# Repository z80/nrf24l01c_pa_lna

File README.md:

# Radio board with Power Amplifier.

A 2.4GHz generic radio communication board based on NRF24L01+ Nordic radio chip and RFX2101C Power Amplifier chip.

It is equipped with an on-board 3.3V linear regulator. So, it hasn't ever been noticed loosing a connection or malfunctioning due to power rail voltage fluctuations if powered with anything above 3.7V.

Thermal design turned out to be good. At max power and constant carrier mode the board consumes ~200mA of current. But neither part gets hot. The whole board heats up evenly and is just warm on touch.

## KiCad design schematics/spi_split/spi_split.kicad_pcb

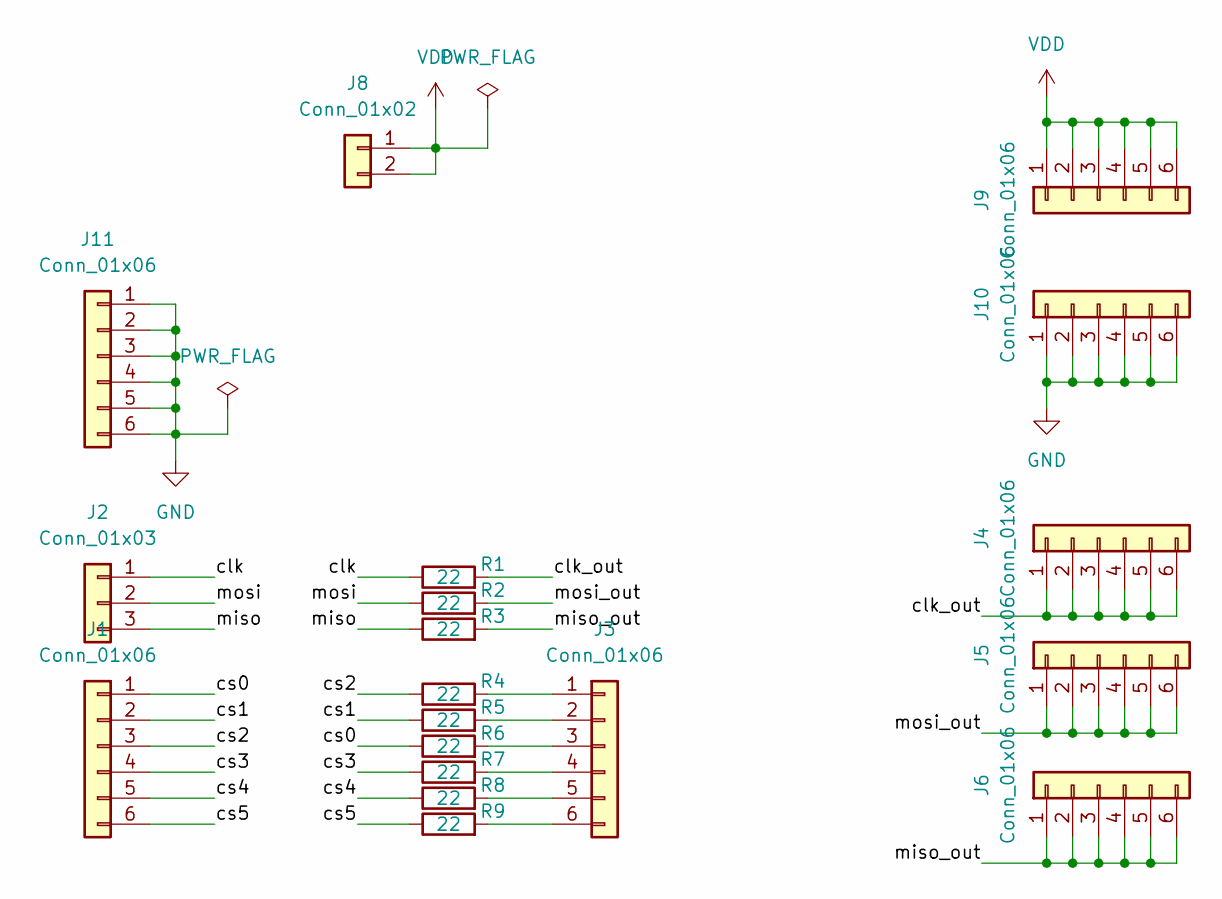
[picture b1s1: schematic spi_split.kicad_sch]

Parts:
J1, J3, J4, J5, J6, J9, J10, J11: Conn_01x06; PinHeader_1x06_P2.54mm_Vertical
J2: Conn_01x03; PinHeader_1x03_P2.54mm_Vertical
J8: Conn_01x02; PinHeader_1x02_P2.54mm_Vertical
R1, R2, R3, R4, R5, R6, R7, R8, R9: 22; R_0603_1608Metric

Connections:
/clk: J2.1, R1.1
/clk_out: J4.1, J4.2, J4.3, J4.4, J4.5, J4.6, R1.2
/cs0: J1.1, R6.1
/cs1: J1.2, R5.1
/cs2: J1.3, R4.1
/cs3: J1.4, R7.1
/cs4: J1.5, R8.1
/cs5: J1.6, R9.1
/miso: J2.3, R3.1
/miso_out: J6.1, J6.2, J6.3, J6.4, J6.5, J6.6, R3.2
/mosi: J2.2, R2.1
/mosi_out: J5.1, J5.2, J5.3, J5.4, J5.5, J5.6, R2.2
GND: J10.1, J10.2, J10.3, J10.4, J10.5, J10.6, J11.1, J11.2, J11.3, J11.4, J11.5, J11.6
unnamed: J3.1, R4.2
unnamed: J3.2, R5.2
unnamed: J3.3, R6.2
unnamed: J3.4, R7.2
unnamed: J3.5, R8.2
unnamed: J3.6, R9.2
VDD: J8.1, J8.2, J9.1, J9.2, J9.3, J9.4, J9.5, J9.6

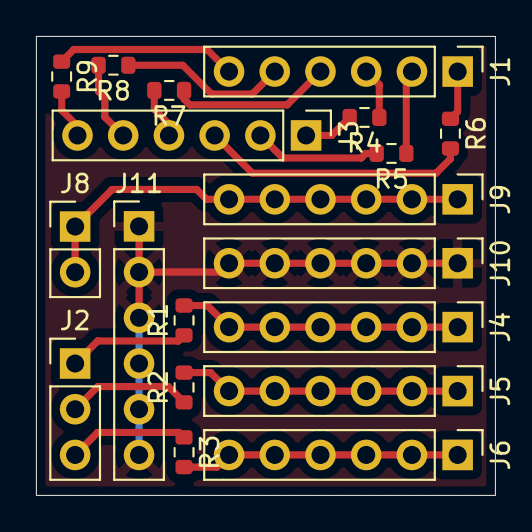
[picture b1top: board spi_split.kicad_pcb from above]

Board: 2 copper layers, 25.5 x 25.5 mm, 19 parts (0 on the bottom side), 20 nets.

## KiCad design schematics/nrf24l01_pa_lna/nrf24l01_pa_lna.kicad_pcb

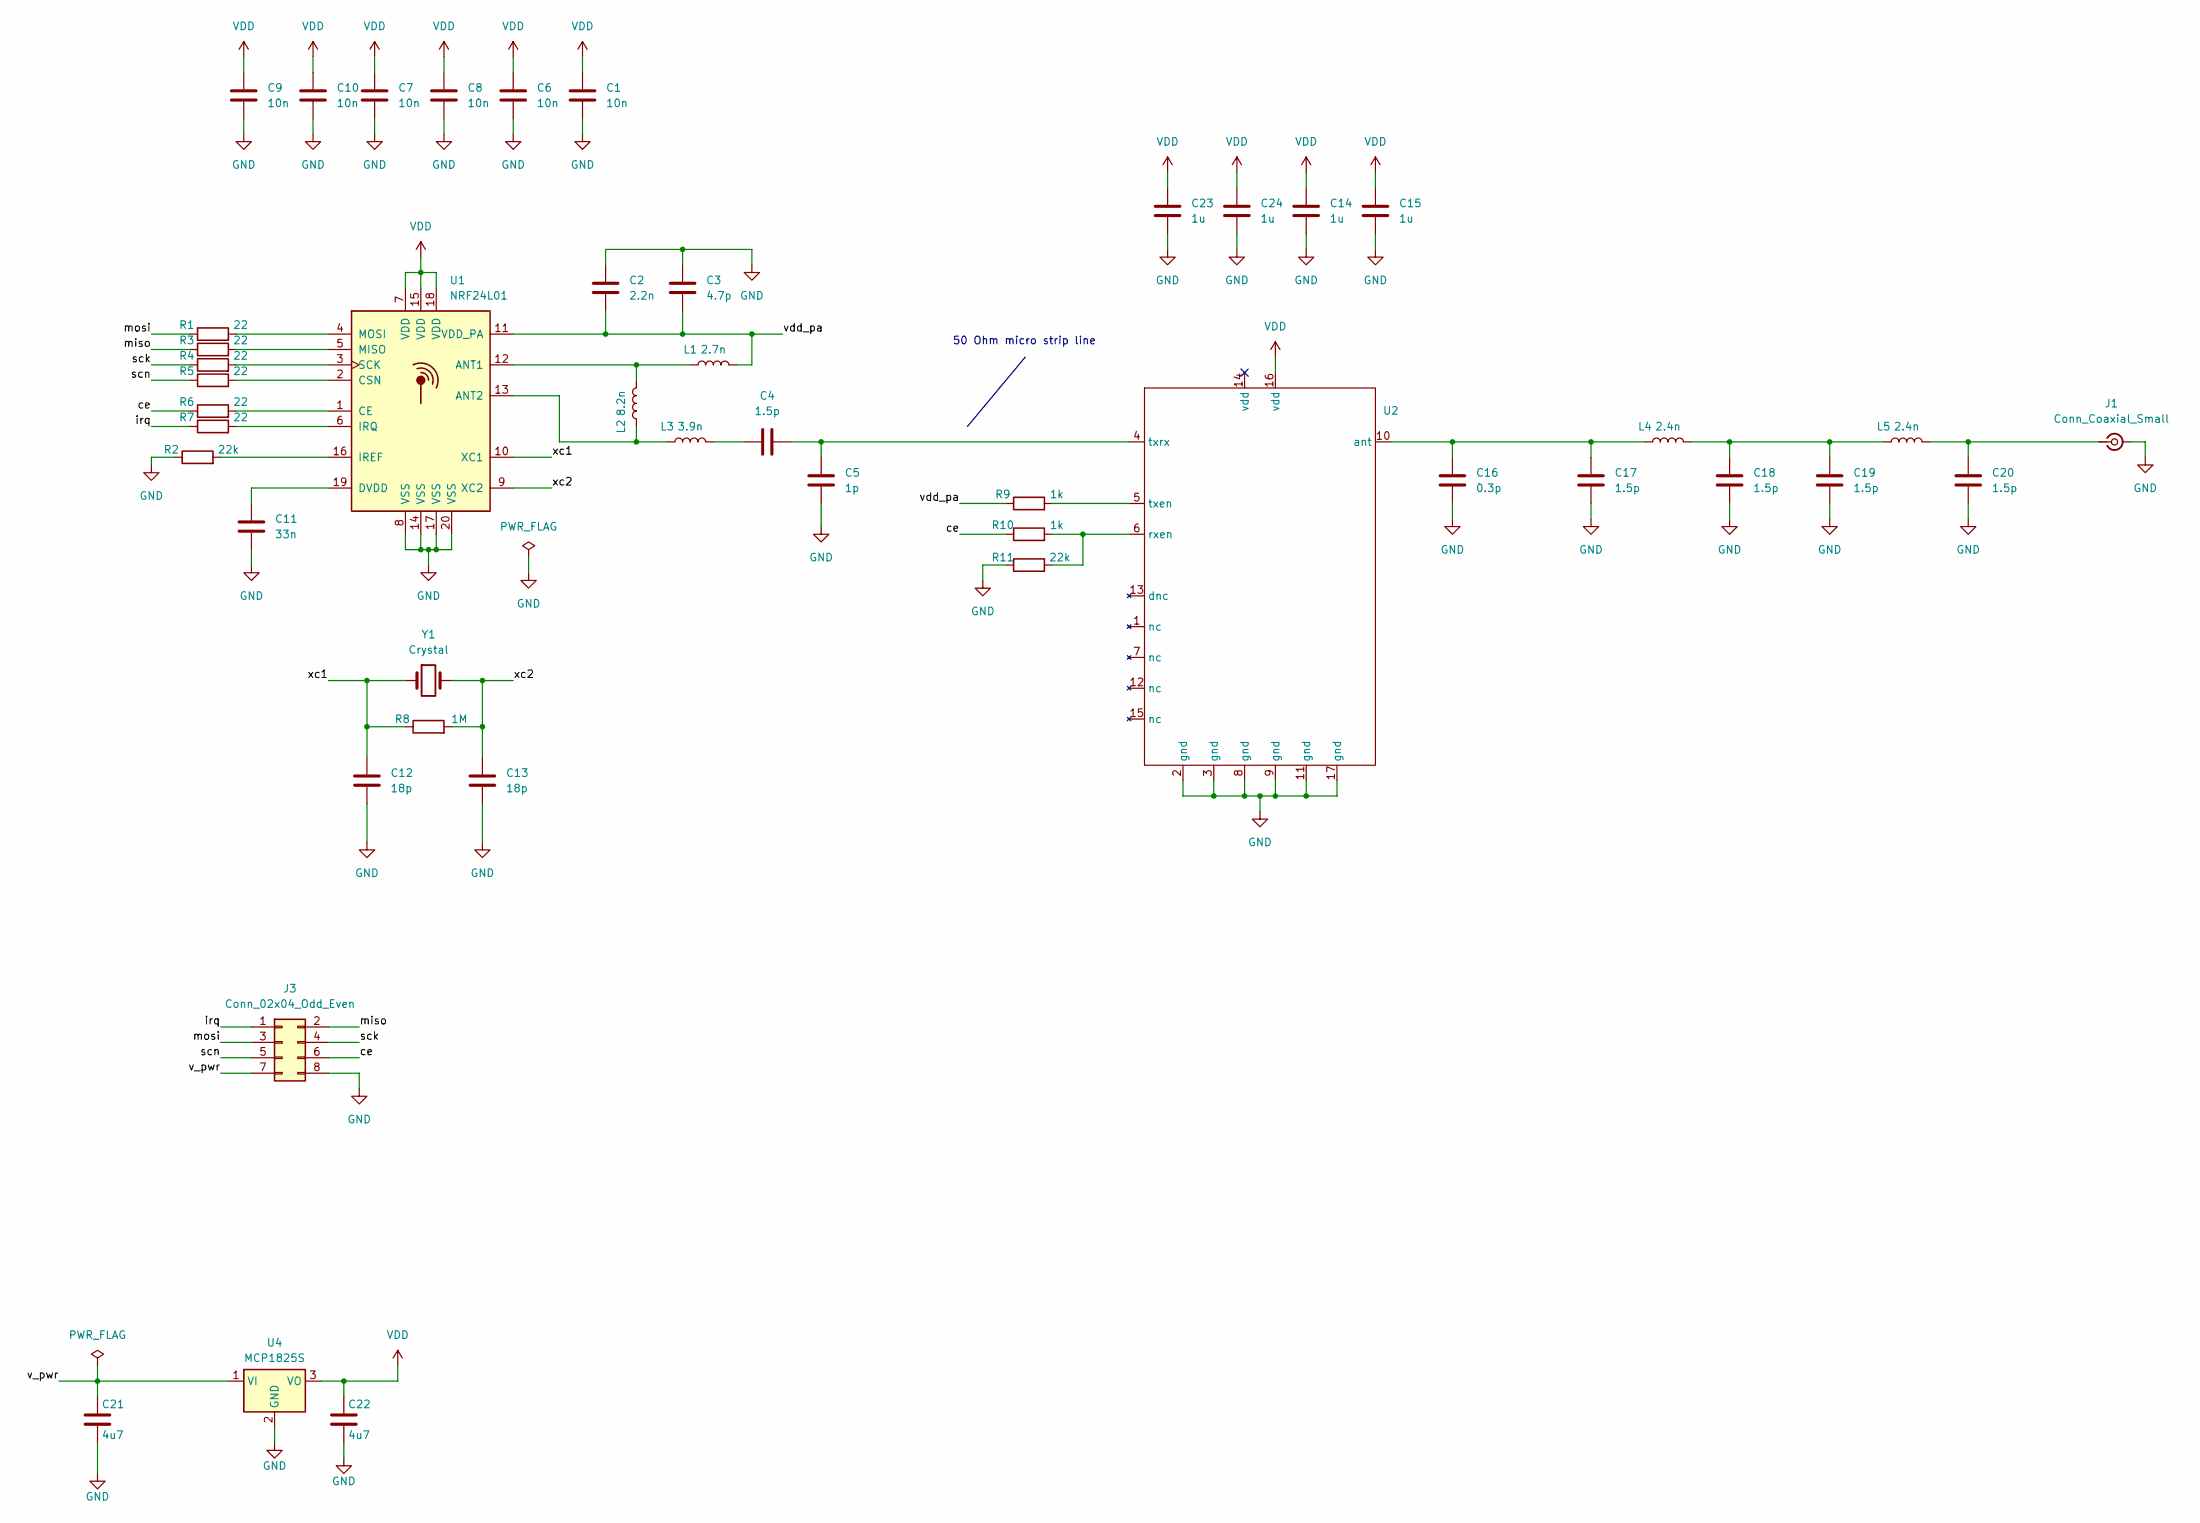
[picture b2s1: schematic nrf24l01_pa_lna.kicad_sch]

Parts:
C1, C6, C7, C8, C9, C10: 10n; C_0402_1005Metric
C2: 2.2n; C_0402_1005Metric
C3: 4.7p; C_0402_1005Metric
C4, C17, C18, C19, C20: 1.5p; C_0402_1005Metric
C5: 1p; C_0402_1005Metric
C11: 33n; C_0402_1005Metric
C12, C13: 18p; C_0402_1005Metric
C14, C15, C23, C24: 1u; C_0402_1005Metric
C16: 0.3p; C_0402_1005Metric
C21, C22: 4u7; C_0603_1608Metric
J1: Conn_Coaxial_Small; SMA_Amphenol_132289_EdgeMount
J3: Conn_02x04_Odd_Even; PinHeader_2x04_P2.54mm_Vertical
L1: 2.7n; L_0402_1005Metric
L2: 8.2n; L_0402_1005Metric
L3: 3.9n; L_0402_1005Metric
L4, L5: 2.4n; L_0402_1005Metric
R1, R3, R4, R5, R6, R7: 22; R_0402_1005Metric
R2, R11: 22k; R_0402_1005Metric
R8: 1M; R_0402_1005Metric
R9, R10: 1k; R_0402_1005Metric
U1: NRF24L01; QFN-20-4x4mm_P0.5mm_EP2.5x2.5mm
U2: LQFN-16-1EP_3x3mm_P0.5mm_EP1.7x1.7mm
U4: MCP1825S; SOT-223-3_TabPin2
Y1: Crystal; Crystal_HC18-U_Vertical

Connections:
/ce: J3.6, R6.1, R10.1
/irq: J3.1, R7.1
/miso: J3.2, R3.1
/mosi: J3.3, R1.1
/sck: J3.4, R4.1
/scn: J3.5, R5.1
/v_pwr: C21.1, J3.7, U4.1 (VI)
/vdd_pa: C2.2, C3.2, L1.2, R9.1, U1.11 (VDD_PA)
/xc1: C12.1, R8.1, U1.10 (XC1), Y1.1
/xc2: C13.1, R8.2, U1.9 (XC2), Y1.2
GND: C1.2, C2.1, C3.1, C5.1, C6.2, C7.2, C8.2, C9.2, C10.2, C11.2, C12.2, C13.2, C14.2, C15.2, C16.1, C17.1, C18.1, C19.1, C20.1, C21.2, C22.2, C23.2, C24.2, J1.2 (Ext), J3.8, R2.1, R11.1, U1.8 (VSS), U1.14 (VSS), U1.17 (VSS), U1.20 (VSS), U2.2 (gnd), U2.3 (gnd), U2.8 (gnd), U2.9 (gnd), U2.11 (gnd), U2.17 (gnd), U4.2 (GND)
unnamed: C4.1, L3.2
unnamed: C18.2, C19.2, L4.2, L5.1
unnamed: C20.2, J1.1 (In), L5.2
unnamed: L1.1, L2.2, U1.12 (ANT1)
unnamed: L2.1, L3.1, U1.13 (ANT2)
unnamed: R6.2, U1.1 (CE)
unnamed: R5.2, U1.2 (CSN)
unnamed: C11.1, U1.19 (DVDD)
unnamed: R2.2, U1.16 (IREF)
unnamed: R7.2, U1.6 (IRQ)
unnamed: R3.2, U1.5 (MISO)
unnamed: R1.2, U1.4 (MOSI)
unnamed: R4.2, U1.3 (SCK)
unnamed: C16.2, C17.2, L4.1, U2.10 (ant)
unnamed: R10.2, R11.2, U2.6 (rxen)
unnamed: R9.2, U2.5 (txen)
unnamed: C4.2, C5.2, U2.4 (txrx)
VDD: C1.1, C6.1, C7.1, C8.1, C9.1, C10.1, C14.1, C15.1, C22.1, C23.1, C24.1, U1.7 (VDD), U1.15 (VDD), U1.18 (VDD), U2.16 (vdd), U4.3 (VO)

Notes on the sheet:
50 Ohm micro strip line

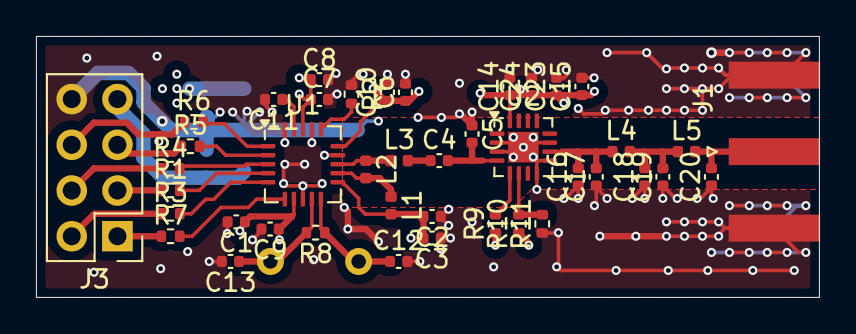
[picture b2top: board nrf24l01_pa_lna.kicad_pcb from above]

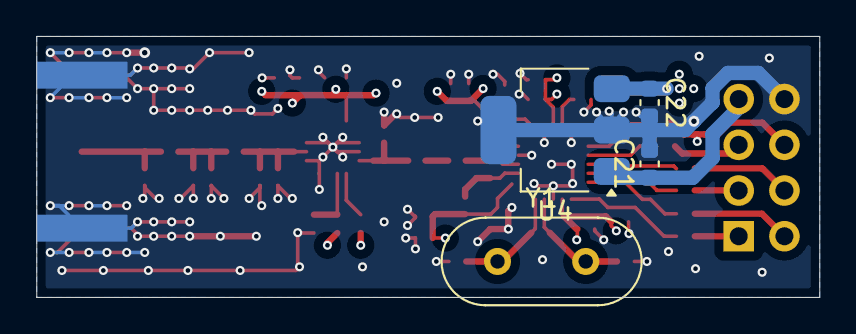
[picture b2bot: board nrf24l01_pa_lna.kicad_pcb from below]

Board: 4 copper layers, 43.5 x 14.5 mm, 46 parts (4 on the bottom side), 29 nets.

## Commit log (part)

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2026-01-14 Designing the schematic and picking specific components.
2026-01-14 Power flags to avoid KiCad errors.
2026-01-14 Placing elements, making connections.
2026-01-15 Finished the design in bulk...
2026-01-17 May be good enough?
2026-01-19 Generated interactive BOM.
2026-01-19 Making antenna jig.
2026-01-19 Jig and spacer.
2026-02-11 Downloaded a python driver for NRF32L01. The bring up tests.
2026-02-14 Tests run. Probably means that at least the digital part of the RF chip works.
2026-02-15 A fix plus needed functionality.
2026-02-15 Jig STL files.
2026-02-16 Transmit-receive works.
2026-02-16 Constant carrier with changing channel also runs. At max power the board gets warm, but not hot.
2026-02-16 Channels information.
2026-02-21 Making cases.
2026-02-21 PCB case.
2026-02-28 Designing const carrier...
2026-02-28 Adjustments to the standoff design.
2026-03-01 Forgot to import Pin from pyb.
2026-03-01 Periodic one seem to work better.
2026-03-15 This is unrelated. Sending controls to ps5.
2026-03-15 Board for splitting SPI to multiple slaves, up to 6 slave boards.
2026-03-15 Light stand. This is unrelated. Just put it here.
2026-03-22 Generated BOM for the SPI split board.
2026-04-28 Desnging board mounts.
2026-05-14 Modified driver to have an option to instantiate it a few times with different pins but the same SPI.
2026-05-16 With insert.
2026-05-18 Joint light stand.
2026-05-18 This way it works. Need to initialize all the pins such that neither CS pin is low.
2026-05-28 Added README.md.
